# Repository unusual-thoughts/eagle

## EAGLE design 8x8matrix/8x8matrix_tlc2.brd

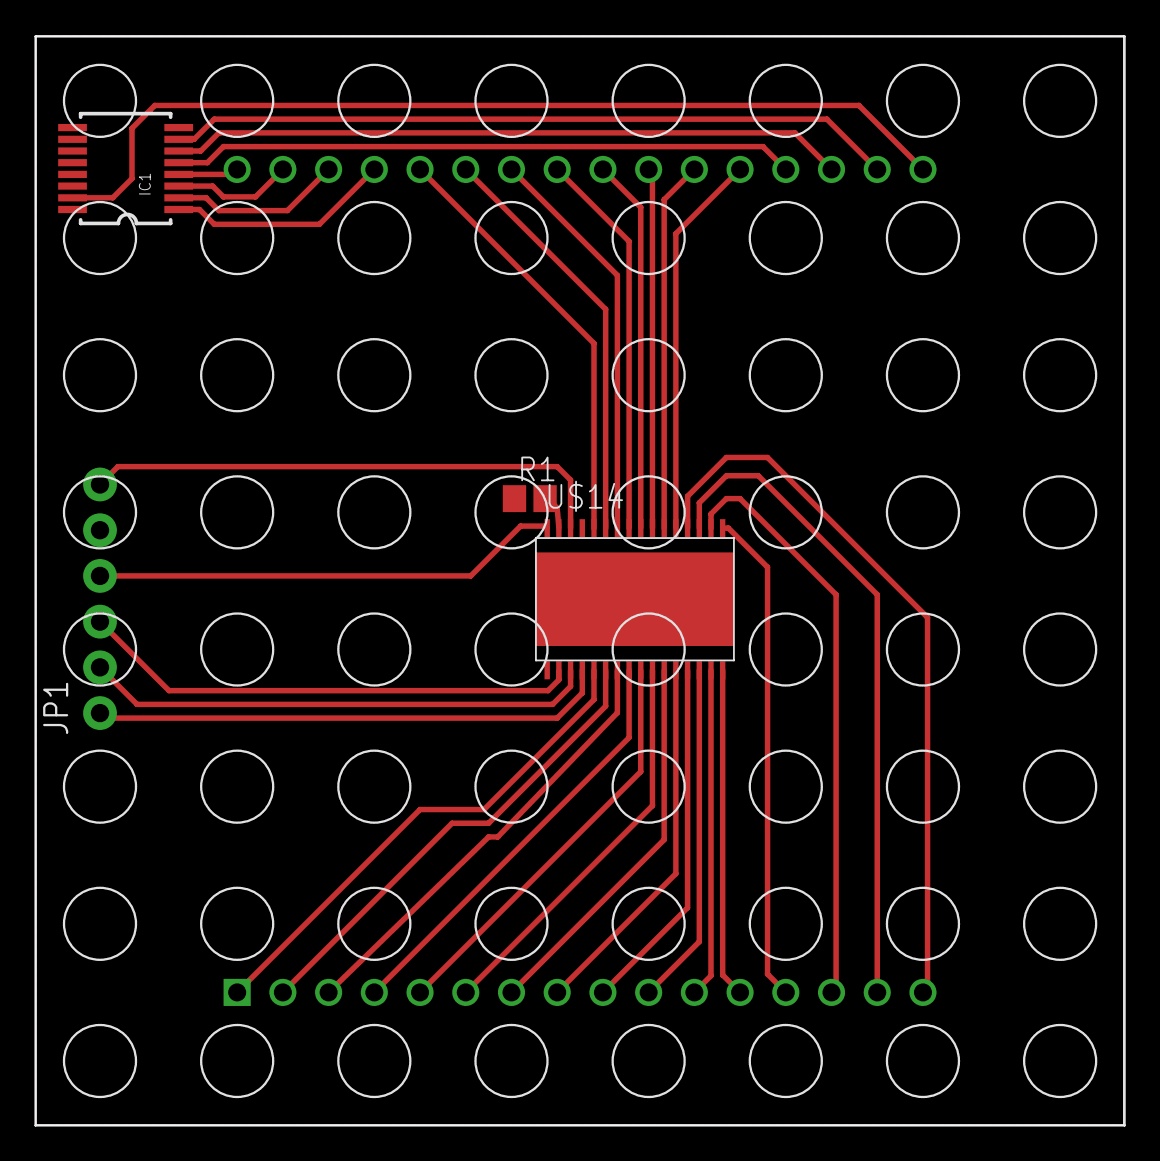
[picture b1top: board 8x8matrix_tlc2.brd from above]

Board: 2 copper layers, 60.4 x 60.5 mm, 5 parts (0 on the bottom side), 39 nets.

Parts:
IC1: 74595; TSSOP16
JP1: 1X06
R1: R0805
U$1: 8X8MATRIX
U$14: TLC5947DAP; HTSSOP32DAP

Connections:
5.0V: IC1.16, JP1.4, U$14.32
BLANK: JP1.3, U$14.2
GND: IC1.8, JP1.5, R1.1, U$14.1, U$14.EXP
unnamed: U$1.P1, U$14.5
unnamed: U$1.P2, U$14.6
unnamed: U$1.P3, U$14.7
unnamed: U$1.P4, U$14.8
unnamed: U$1.P5, U$14.9
unnamed: U$1.P6, U$14.10
unnamed: U$1.P7, U$14.11
unnamed: U$1.P8, U$14.12
unnamed: U$1.P9, U$14.13
unnamed: U$1.P10, U$14.14
unnamed: U$1.P11, U$14.15
unnamed: U$1.P12, U$14.16
unnamed: U$1.P13, U$14.17
unnamed: U$1.P14, U$14.18
unnamed: U$1.P15, U$14.19
unnamed: U$1.P16, U$14.20
unnamed: U$1.P21, U$14.21
unnamed: U$1.P22, U$14.22
unnamed: U$1.P23, U$14.23
unnamed: U$1.P24, U$14.24
unnamed: U$1.P25, U$14.25
unnamed: U$1.P26, U$14.26
unnamed: U$1.P27, U$14.27
unnamed: U$1.P28, U$14.28
unnamed: IC1.1, U$1.P29
unnamed: IC1.2, U$1.P30
unnamed: R1.2, U$14.31
unnamed: JP1.2, U$14.3
unnamed: IC1.3, U$1.P31
unnamed: IC1.4, U$1.P32
unnamed: IC1.5, U$1.P20
unnamed: IC1.6, U$1.P19
unnamed: IC1.7, U$1.P18
unnamed: IC1.15, U$1.P17
SIN: JP1.1, U$14.4
XLAT: JP1.6, U$14.30

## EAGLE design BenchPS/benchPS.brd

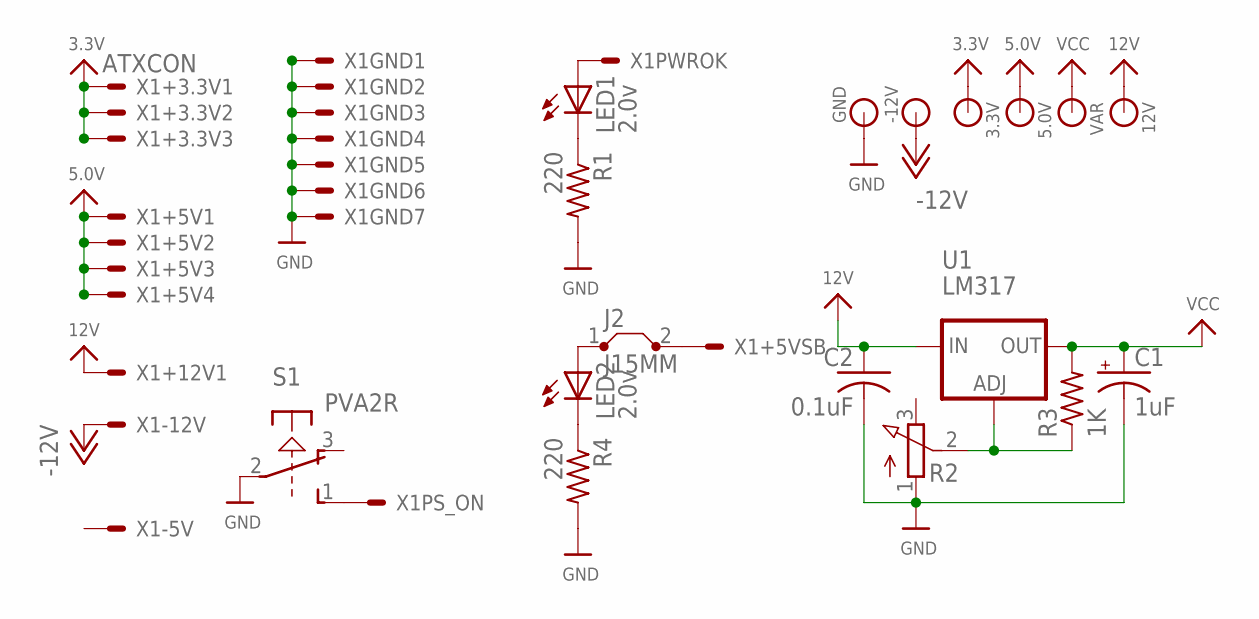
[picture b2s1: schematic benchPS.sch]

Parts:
3.3V, 5.0V, 12V: BANANA_CONN
-12V: BANANA_CONN
C1: 1uF; E3,5-8
C2: 0.1uF; C050-025X075
GND: BANANA_CONN
J2: J15MM; 15
LED1, LED2: 2.0v; LED3MM
R1, R4: 220; 0204/7
R2: 3RP/1610N
R3: 1K; 0204/7
S1: PVA2R
U1: LM317; TO220-ADJ
VAR: BANANA_CONN
X1: ATXCON; 5566-20

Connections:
3.3V: 3.3V.P$1, X1.1, X1.2, X1.11
5.0V: 5.0V.P$1, X1.4, X1.6, X1.19, X1.20
12V: 12V.P$1, C2.1, U1.IN, X1.10
-12V: -12V.P$1, X1.12
GND: C1.-, C2.2, GND.P$1, R1.2, R2.1 (A), R4.2, S1.2, X1.3, X1.5, X1.7, X1.13, X1.15, X1.16, X1.17
unnamed: LED1.A, X1.8
unnamed: LED1.K (C), R1.1
unnamed: S1.1 (S), X1.14
unnamed: R2.2 (S), R3.1, U1.ADJ
unnamed: J2.2, X1.9
unnamed: LED2.K (C), R4.1
unnamed: J2.1, LED2.A
VCC: C1.+, R3.2, U1.OUT, VAR.P$1

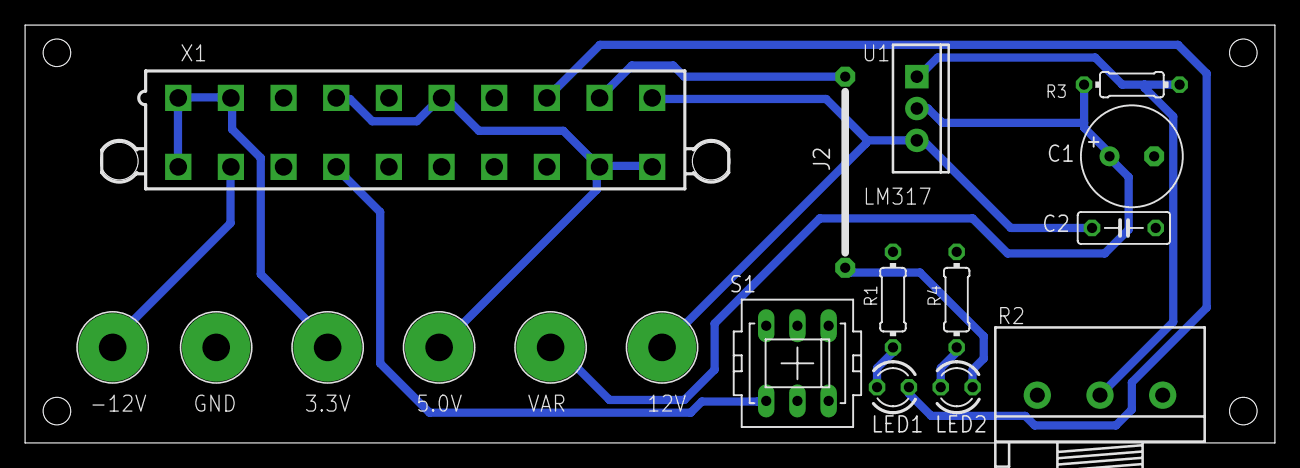
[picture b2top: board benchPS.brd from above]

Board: 2 copper layers, 99.7 x 33.3 mm, 18 parts (0 on the bottom side), 13 nets.

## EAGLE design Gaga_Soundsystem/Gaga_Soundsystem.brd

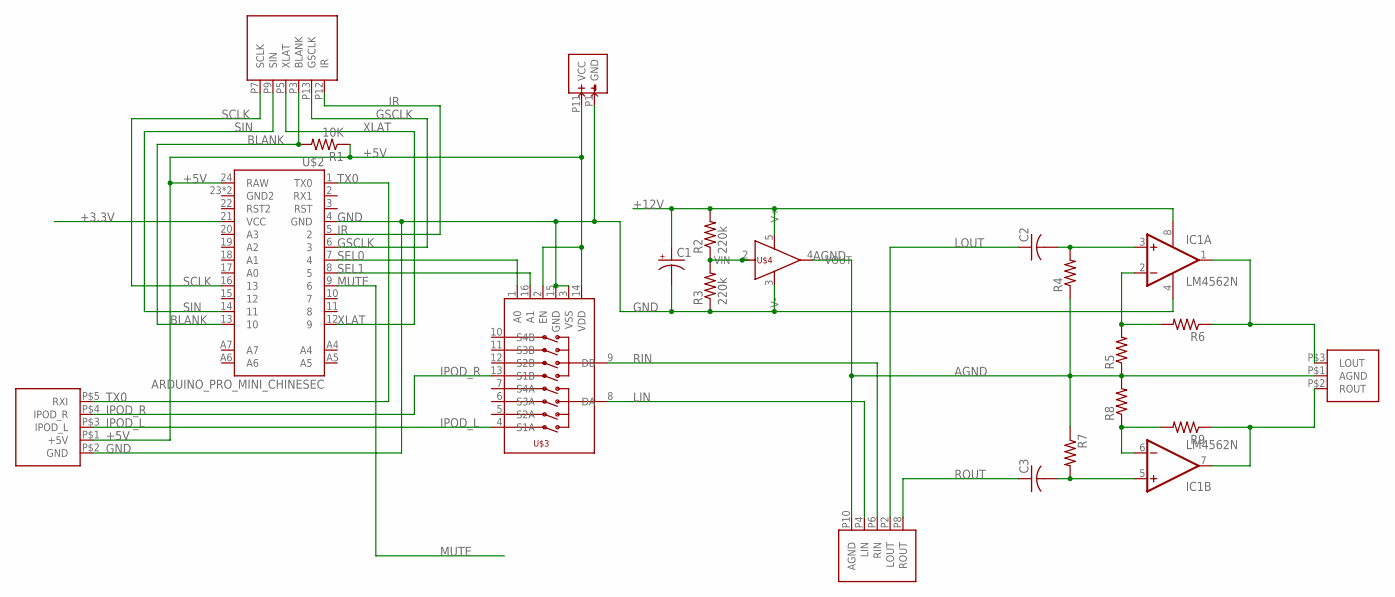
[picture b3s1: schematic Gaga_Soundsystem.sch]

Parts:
C1: CPOL-USE5-13; E5-13
C2, C3: C-US075-063X106; C075-063X106
IC1: LM4562N; DIL08
R1: 10K; 0207/7
R2, R3: 220k; 0207/7
R4, R5, R6, R7, R8, R9: R-US_0207/7; 0207/7
U$1: OTHERSIDE
U$2: ARDUINO_PRO_MINI_CHINESEC; ARDUINO_PRO_MINI_CHINESE
U$3: ADG709; TSSOP16
U$4: BUF634; TO220
U$5: IPODCON
U$6: AUDIOOUT

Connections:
+3.3V: U$2.21 (VCC)
+5V: R1.1, U$1.P11 (VCC), U$2.24 (RAW), U$3.2 (EN), U$3.14 (VDD), U$5.P$1 (+5V)
+12V: C1.+, IC1.8 (V+), R2.2, U$4.5 (V+)
AGND: R4.1, R5.1, R7.1, R8.2, U$1.P10 (AGND), U$4.4 (VOUT), U$6.P$1 (AGND)
BLANK: R1.2, U$1.P3 (BLANK), U$2.13 (10)
GND: C1.-, IC1.4 (V-), R3.1, U$1.P1 (GND), U$2.4 (GND), U$3.3 (VSS), U$3.15 (GND), U$4.3 (V-), U$5.P$2 (GND)
GSCLK: U$1.P13 (GSCLK), U$2.6 (3)
IPOD_L: U$3.4 (S1A), U$5.P$3 (IPOD_L)
IPOD_R: U$3.13 (S1B), U$5.P$4 (IPOD_R)
IR: U$1.P12 (IR), U$2.5 (2)
LIN: U$1.P4 (LIN), U$3.8 (DA)
LOUT: C2.1, U$1.P2 (LOUT)
MUTE: U$2.9 (6)
unnamed: R2.1, R3.2, U$4.2 (VIN)
unnamed: IC1.2 (-IN), R5.2, R6.2
unnamed: C2.2, IC1.3 (+IN), R4.2
unnamed: IC1.6 (-IN), R8.1, R9.2
unnamed: IC1.1 (OUT), R6.1, U$6.P$3 (LOUT)
unnamed: C3.2, IC1.5 (+IN), R7.2
unnamed: IC1.7 (OUT), R9.1, U$6.P$2 (ROUT)
RIN: U$1.P6 (RIN), U$3.9 (DB)
ROUT: C3.1, U$1.P8 (ROUT)
SCLK: U$1.P7 (SCLK), U$2.16 (13)
SEL0: U$2.7 (4), U$3.1 (A0)
SEL1: U$2.8 (5), U$3.16 (A1)
SIN: U$1.P9 (SIN), U$2.14 (11)
TX0: U$2.1 (TX0), U$5.P$5 (RXI)
XLAT: U$1.P5 (XLAT), U$2.12 (9)

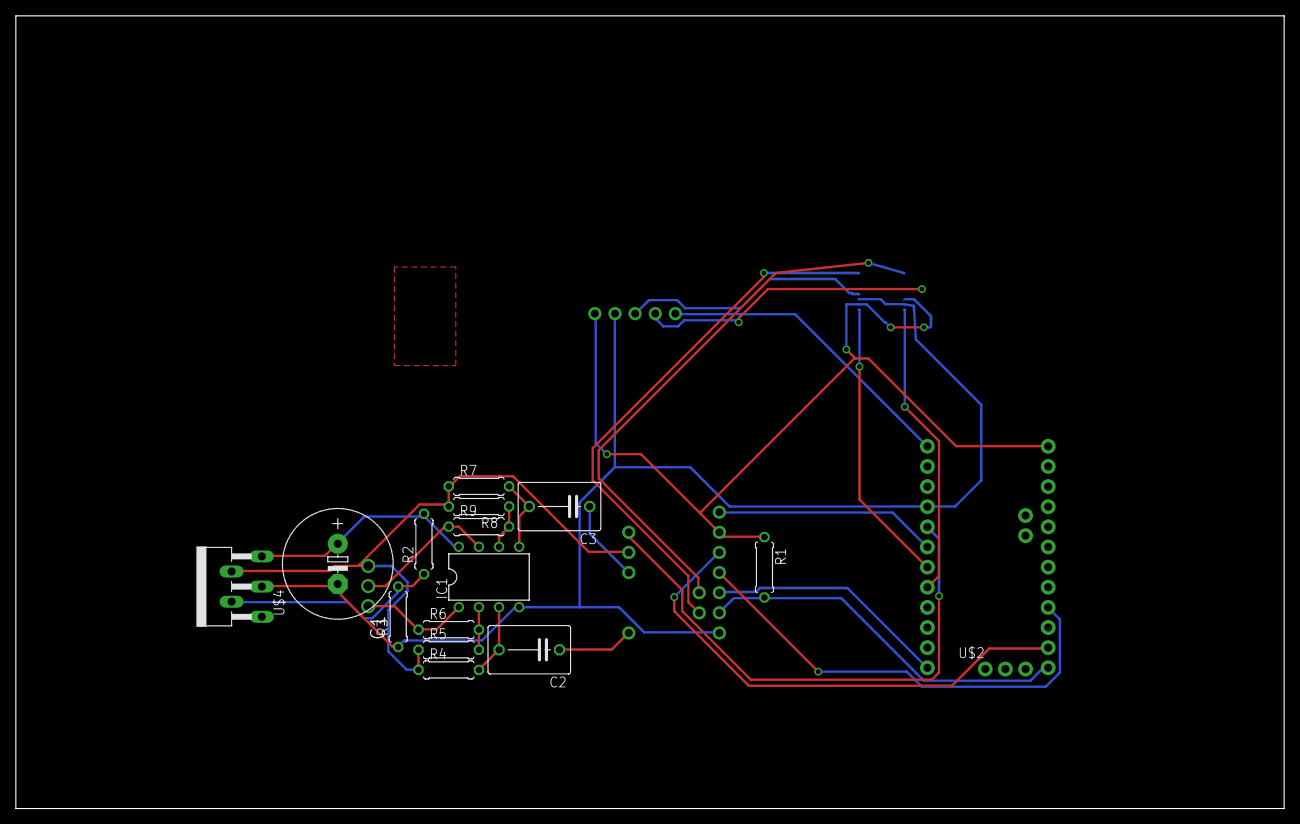
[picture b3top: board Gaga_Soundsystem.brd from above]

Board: 2 copper layers, 160.0 x 100.0 mm, 19 parts (1 on the bottom side), 26 nets.

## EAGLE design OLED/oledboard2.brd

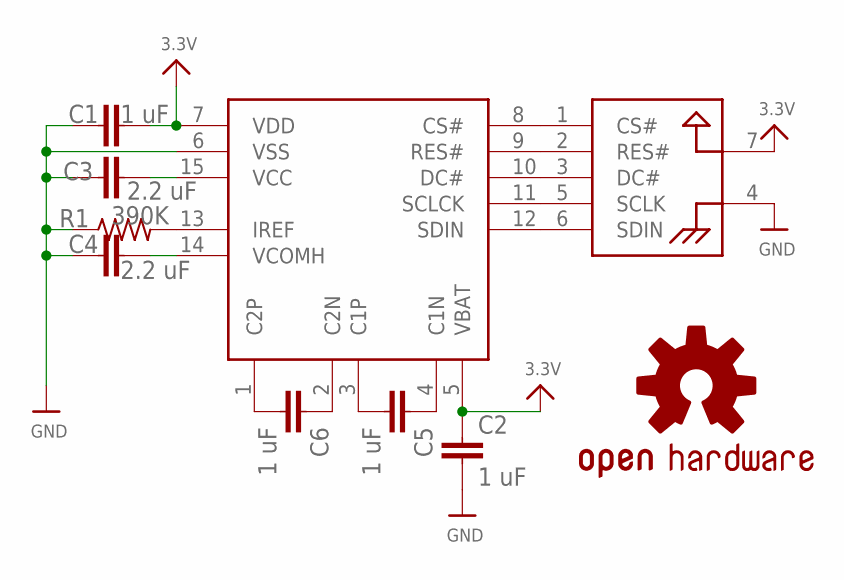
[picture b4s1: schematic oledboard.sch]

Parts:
C1, C2, C5, C6: 1 uF; C0805
C3, C4: 2.2 uF; C0805
LOGO1: OSHW.SYMS; OSHW-LOGO-S
R1: 390K; R0805
U$1: UG-2832HSWEG04
U$6: CONNECTOR

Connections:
3.3V: C1.2, C2.1, U$1.5 (VBAT), U$1.7 (VDD), U$6.7 (GND)
GND: C1.1, C2.2, C3.1, C4.1, R1.1, U$1.6 (VSS), U$6.4 (3.3V)
unnamed: C5.1, U$1.4 (C1N)
unnamed: C5.2, U$1.3 (C1P)
unnamed: C6.1, U$1.2 (C2N)
unnamed: C6.2, U$1.1 (C2P)
unnamed: R1.2, U$1.13 (IREF)
unnamed: U$1.8 (CS#), U$6.1 (CS#)
unnamed: C3.2, U$1.15 (VCC)
unnamed: C4.2, U$1.14 (VCOMH)
unnamed: U$1.9 (RES#), U$6.2 (RES#)
unnamed: U$1.10 (DC#), U$6.3 (DC#)
unnamed: U$1.11 (SCLCK), U$6.5 (SCLK)
unnamed: U$1.12 (SDIN), U$6.6 (SDIN)

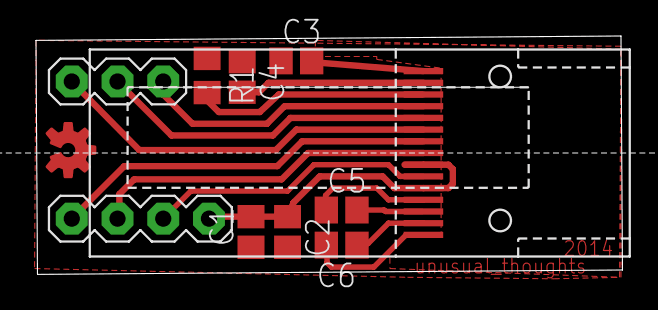
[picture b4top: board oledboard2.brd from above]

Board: 2 copper layers, 32.6 x 13.2 mm, 10 parts (0 on the bottom side), 14 nets.

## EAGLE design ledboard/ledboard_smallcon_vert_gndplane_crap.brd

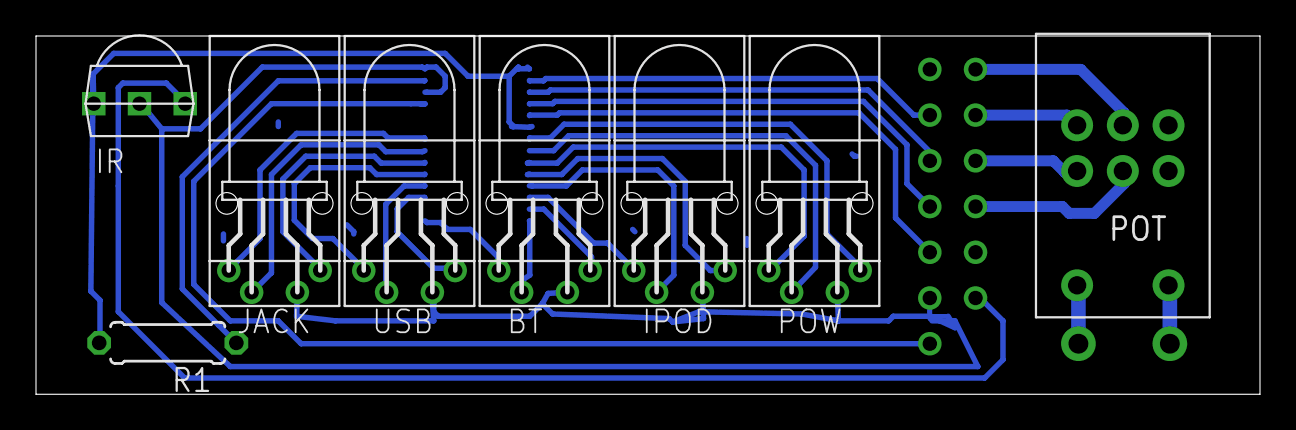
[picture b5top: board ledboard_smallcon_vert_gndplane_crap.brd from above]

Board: 2 copper layers, 68.0 x 19.9 mm, 10 parts (1 on the bottom side), 31 nets.

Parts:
BT: 5MMRGBLEDBENT; BENTLED
IPOD: 5MMRGBLEDBENT; BENTLED
IR: TSOP323
JACK: 5MMRGBLEDBENT; BENTLED
POT: ALPS_RK0971221Z0X
POW: 5MMRGBLEDBENT; BENTLED
R1: 2K; 0207/7
U$1: TLC5941; HTSSOP28_POWERPAD
U$3: CONNECTORSMALL4; SMALLL4
USB: 5MMRGBLEDBENT; BENTLED

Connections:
12VIN: POT.S1, U$3.1
12VOUT: POT.S2, U$3.2
AGND: POT.G1, POT.G2, U$3.7
GND: IR.P3, R1.2, U$1.1, U$1.6, U$1.PAD, U$3.6
GSCLK: U$1.25, U$3.3
LIN: POT.I1, U$3.10
LOUT: POT.O1, U$3.11
N1: POW.P$1, U$1.9
unnamed: U$1.2, U$3.15
unnamed: POW.P$4, U$1.7
unnamed: POW.P$2, U$1.8
unnamed: IPOD.P$4, U$1.10
unnamed: IPOD.P$2, U$1.11
unnamed: IPOD.P$1, U$1.12
unnamed: BT.P$4, U$1.13
unnamed: BT.P$1, U$1.15
unnamed: U$1.19, USB.P$1
unnamed: JACK.P$1, U$1.22
unnamed: BT.P$2, U$1.14
unnamed: U$1.17, USB.P$4
unnamed: JACK.P$4, U$1.20
unnamed: U$1.18, USB.P$2
unnamed: JACK.P$2, U$1.21
unnamed: R1.1, U$1.27
unnamed: IR.P1, U$3.5
RIN: POT.I2, U$3.9
ROUT: POT.O2, U$3.8
SCLK: U$1.4, U$3.13
SIN: U$1.5, U$3.12
VCC: BT.P$3, IPOD.P$3, IR.P2, JACK.P$3, POW.P$3, U$1.26, U$1.28, U$3.4, USB.P$3
XLAT: U$1.3, U$3.14

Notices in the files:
parts and their libraries:
SparkFun-Connectors: Licensing: Creative Commons ShareAlike 4.0 International - https://creativecommons.org/licenses/by-sa/4.0
SparkFun-Connectors: Licensing: CC v3.0 Share-Alike You are welcome to use this library for commercial purposes.
